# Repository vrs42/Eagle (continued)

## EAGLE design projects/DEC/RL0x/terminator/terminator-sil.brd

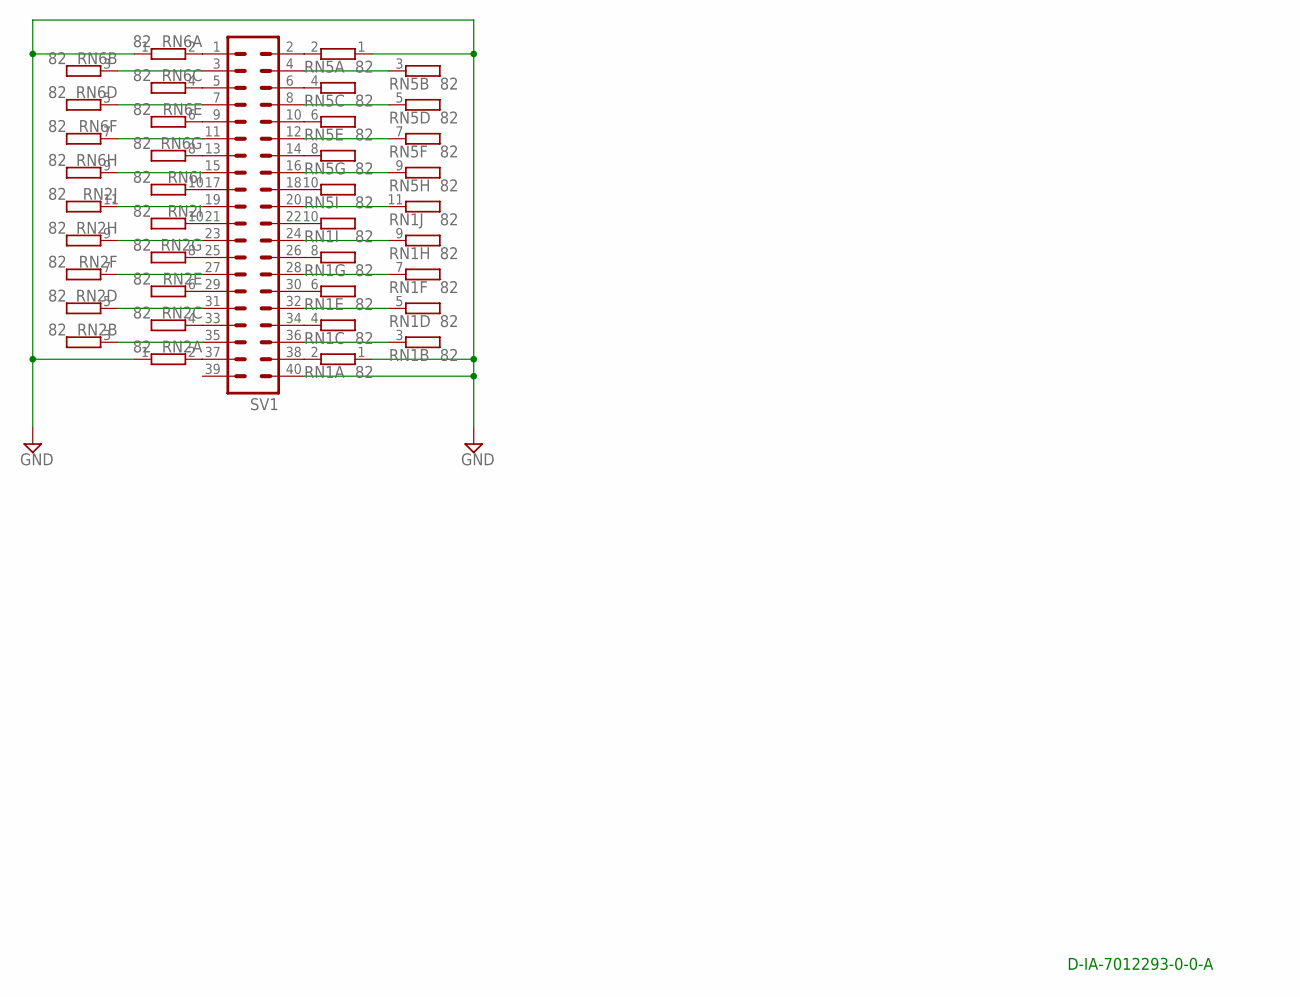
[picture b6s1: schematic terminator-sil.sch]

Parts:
RN1, RN2: 82; SIL11
RN5, RN6: 82; SIL10
SV1: MA20-2

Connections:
GND: RN1.1, RN2.1, RN5.1, RN6.1, SV1.40
unnamed: RN1.2, SV1.38
unnamed: RN1.3 (2), SV1.36
unnamed: RN1.4 (2), SV1.34
unnamed: RN1.6 (2), SV1.30
unnamed: RN1.8 (2), SV1.26
unnamed: RN1.10 (2), SV1.22
unnamed: RN5.10 (2), SV1.18
unnamed: RN5.8 (2), SV1.14
unnamed: RN5.6 (2), SV1.10
unnamed: RN5.4 (2), SV1.6
unnamed: RN5.3 (2), SV1.4
unnamed: RN1.5 (2), SV1.32
unnamed: RN1.7 (2), SV1.28
unnamed: RN1.9 (2), SV1.24
unnamed: RN1.11 (2), SV1.20
unnamed: RN5.9 (2), SV1.16
unnamed: RN5.7 (2), SV1.12
unnamed: RN5.5 (2), SV1.8
unnamed: RN5.2, SV1.2
unnamed: RN2.2, SV1.37
unnamed: RN2.4 (2), SV1.33
unnamed: RN2.6 (2), SV1.29
unnamed: RN2.8 (2), SV1.25
unnamed: RN2.10 (2), SV1.21
unnamed: RN6.10 (2), SV1.17
unnamed: RN6.8 (2), SV1.13
unnamed: RN6.6 (2), SV1.9
unnamed: RN6.4 (2), SV1.5
unnamed: RN6.2, SV1.1
unnamed: RN6.3 (2), SV1.3
unnamed: RN6.5 (2), SV1.7
unnamed: RN6.7 (2), SV1.11
unnamed: RN6.9 (2), SV1.15
unnamed: RN2.3 (2), SV1.35
unnamed: RN2.5 (2), SV1.31
unnamed: RN2.7 (2), SV1.27
unnamed: RN2.9 (2), SV1.23
unnamed: RN2.11 (2), SV1.19

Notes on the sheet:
D-IA-7012293-0-0-A

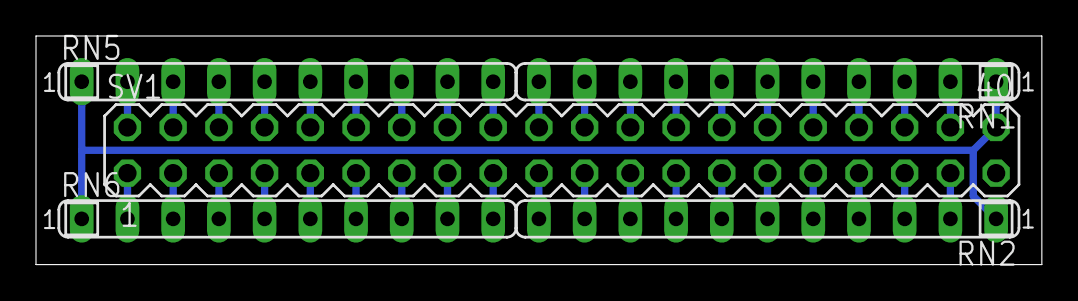
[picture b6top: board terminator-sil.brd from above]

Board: 2 copper layers, 55.9 x 12.7 mm, 5 parts (0 on the bottom side), 39 nets.
